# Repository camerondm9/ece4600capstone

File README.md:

# ece4600capstone
This repository is for storing files related to our Capstone project.

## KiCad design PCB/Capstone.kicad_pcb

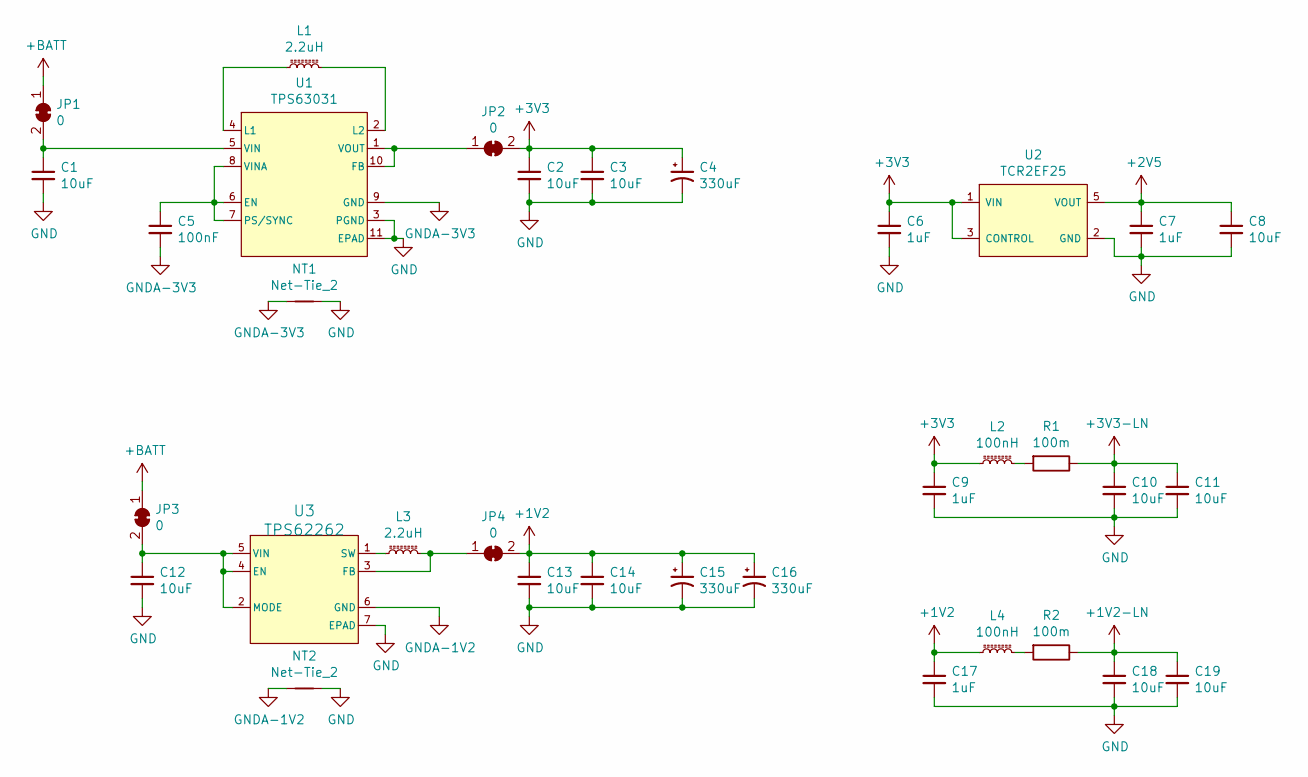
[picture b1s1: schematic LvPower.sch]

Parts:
C1, C2, C3, C8, C10, C11, C12, C13, C14, C18, C19: 10uF; C_0805_HandSoldering
C4, C15, C16: 330uF; CP_Radial_D6.3mm_P2.50mm
C5: 100nF; C_0603_HandSoldering
C6, C7, C9, C17: 1uF; C_0603_HandSoldering
JP1, JP2, JP3, JP4: 0; SolderJumper_0603
L1, L3: 2.2uH; Inductor_Taiyo-Yuden_MD-3030
L2, L4: 100nH; R_0805_HandSoldering
NT1, NT2: Net-Tie_2; NetTie-2
R1, R2: 100m; R_0805_HandSoldering
U1: TPS63031; WSON10-PAD
U2: TCR2EF25; SOT23-5
U3: TPS62262; WSON6-2x2-PAD

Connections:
+1V2: C13.1, C14.1, C15.1, C16.1, C17.1, JP4.2 (B), L4.1; also elsewhere on the board
+1V2-LN: C18.1, C19.1, R2.1; also elsewhere on the board
+2V5: C7.1, C8.1, U2.5 (VOUT); also elsewhere on the board
+3V3: C2.1, C3.1, C4.1, C6.1, C9.1, JP2.2 (B), L2.1, U2.1 (VIN), U2.3 (CONTROL); also elsewhere on the board
+3V3-LN: C10.1, C11.1, R1.1; also elsewhere on the board
+BATT: JP1.1 (A), JP3.1 (A); also elsewhere on the board
GND: C1.2, C2.2, C3.2, C4.2, C6.2, C7.2, C8.2, C9.2, C10.2, C11.2, C12.2, C13.2, C14.2, C15.2, C16.2, C17.2, C18.2, C19.2, NT1.2, NT2.2, U1.3 (PGND), U1.11 (EPAD), U2.2 (GND), U3.7 (EPAD); also elsewhere on the board
GNDA-1V2: NT2.1, U3.6 (GND)
GNDA-3V3: C5.2, NT1.1, U1.9 (GND)
unnamed: C1.1, JP1.2 (B), U1.5 (VIN)
unnamed: C5.1, U1.6 (EN), U1.7 (PS/SYNC), U1.8 (VINA)
unnamed: C12.1, JP3.2 (B), U3.2 (MODE), U3.4 (EN), U3.5 (VIN)
unnamed: JP2.1 (A), U1.1 (VOUT), U1.10 (FB)
unnamed: JP4.1 (A), L3.2, U3.3 (FB)
unnamed: L1.1, U1.4 (L1)
unnamed: L1.2, U1.2 (L2)
unnamed: L2.2, R1.2
unnamed: L3.1, U3.1 (SW)
unnamed: L4.2, R2.2

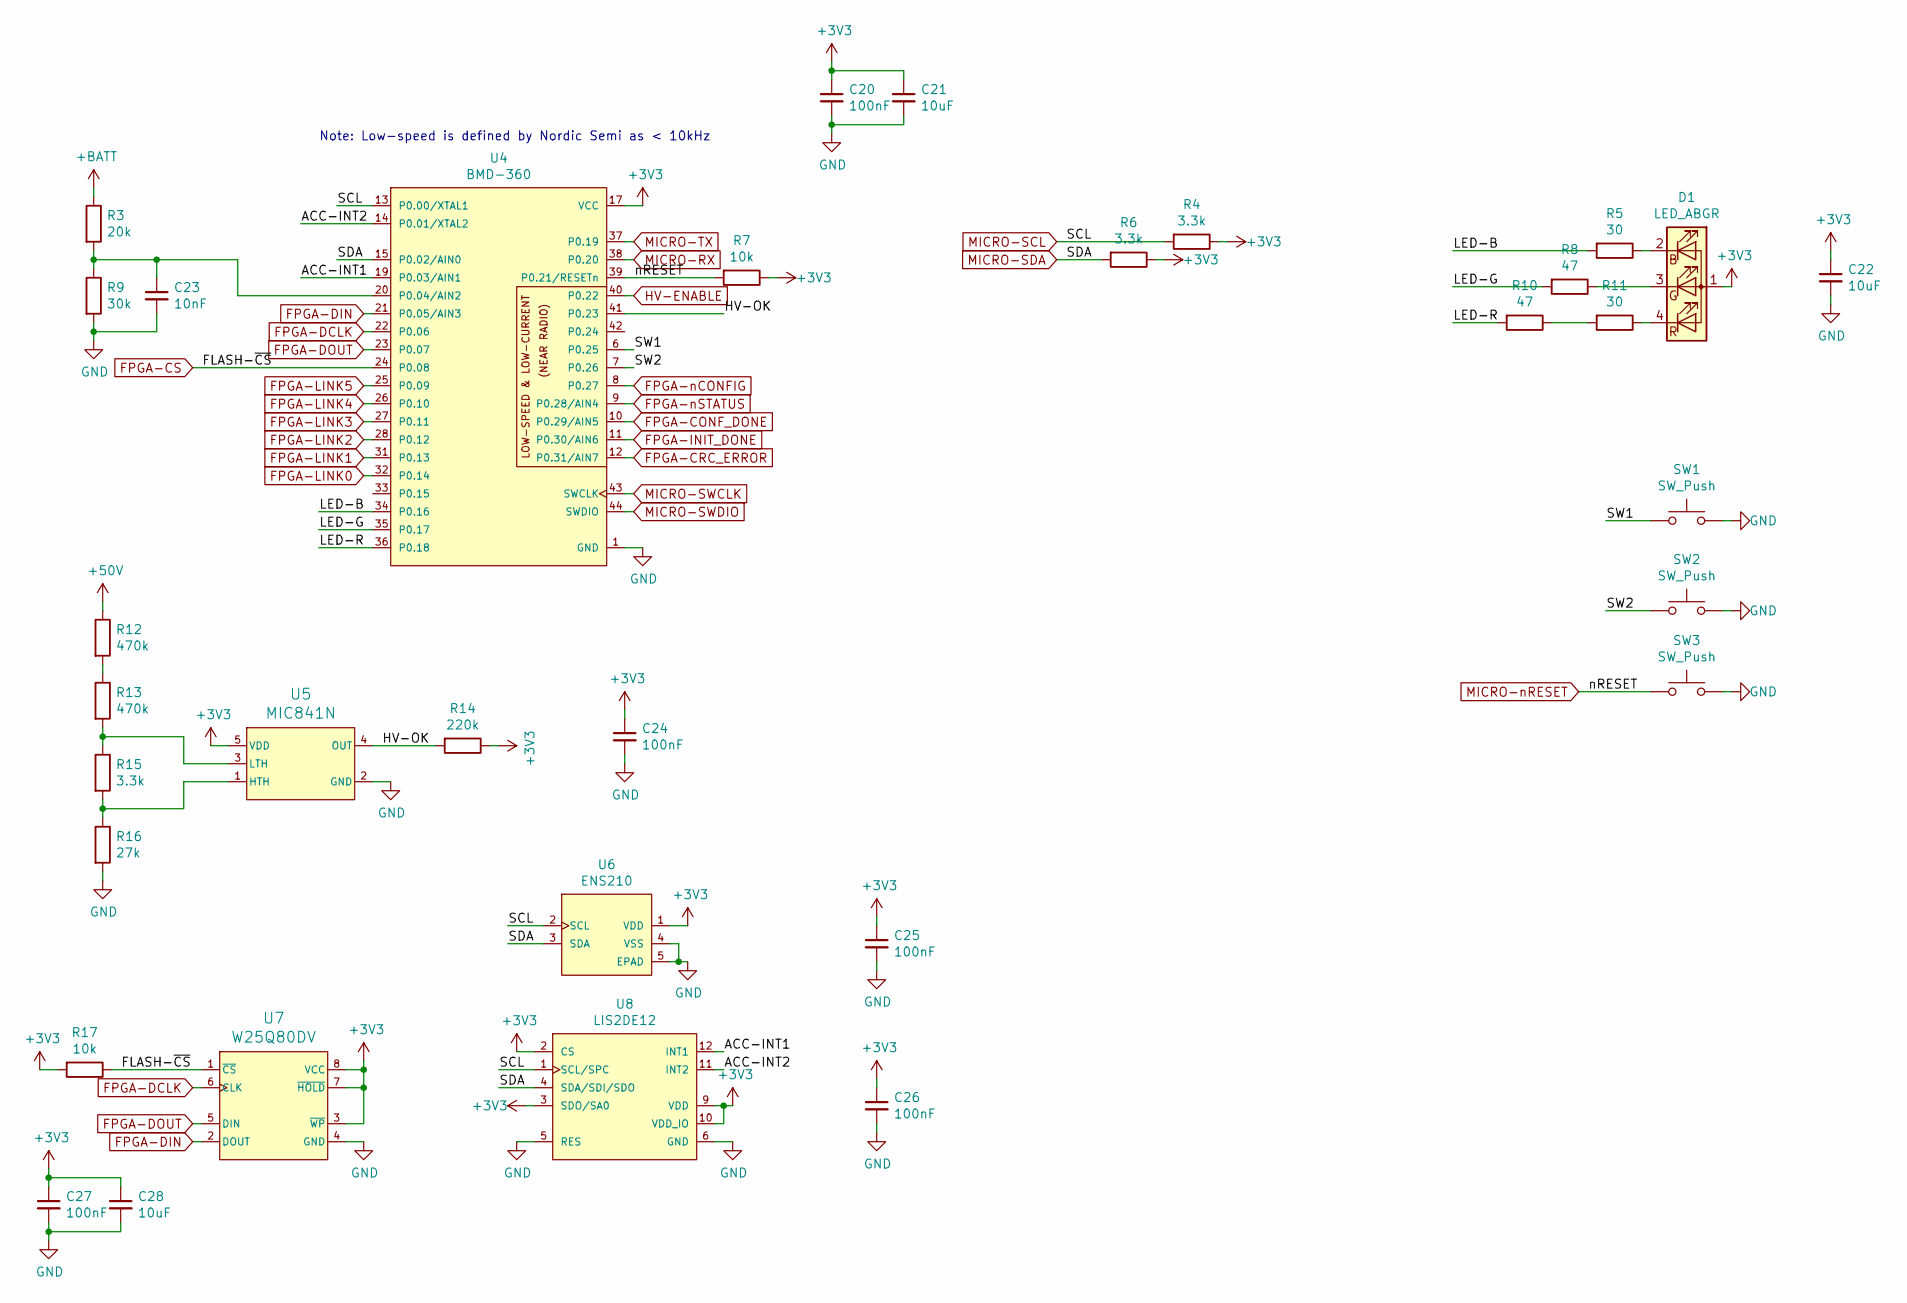
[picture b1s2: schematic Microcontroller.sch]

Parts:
C20, C24, C25, C26, C27: 100nF; C_0603_HandSoldering
C21, C22, C28: 10uF; C_0805_HandSoldering
C23: 10nF; C_0603_HandSoldering
D1: LED_ABGR; CLMVC-FKA
R3: 20k; R_0603_HandSoldering
R4, R6, R15: 3.3k; R_0603_HandSoldering
R5, R11: 30; R_0603_HandSoldering
R7, R17: 10k; R_0603_HandSoldering
R8, R10: 47; R_0603_HandSoldering
R9: 30k; R_0603_HandSoldering
R12, R13: 470k; R_0603_HandSoldering
R14: 220k; R_0603_HandSoldering
R16: 27k; R_0603_HandSoldering
SW1, SW2, SW3: SW_Push; PTS645SK43SM
U4: BMD-360
U5: MIC841N; SOT353
U6: ENS210; QFN4-PAD
U7: W25Q80DV; SOIC8
U8: LIS2DE12; LGA12

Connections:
+3V3: C20.1, C21.1, C22.1, C24.1, C25.1, C26.1, C27.1, C28.1, D1.1 (A), R4.1, R6.1, R7.1, R14.1, R17.2, U4.17 (VCC), U5.5 (VDD), U6.1 (VDD), U7.3 (~WP), U7.7 (~HOLD), U7.8 (VCC), U8.2 (CS), U8.3 (SDO/SA0), U8.9 (VDD), U8.10 (VDD_IO); also elsewhere on the board
+50V: R12.1; also elsewhere on the board
+BATT: R3.1; also elsewhere on the board
/Microcontroller/ACC-INT1: U4.19 (P0.03/AIN1), U8.12 (INT1)
/Microcontroller/ACC-INT2: U4.14 (P0.01/XTAL2), U8.11 (INT2)
/Microcontroller/HV-OK: R14.2, U4.41 (P0.23), U5.4 (OUT)
/Microcontroller/LED-B: R5.2, U4.34 (P0.16)
/Microcontroller/LED-G: R8.2, U4.35 (P0.17)
/Microcontroller/LED-R: R10.2, U4.36 (P0.18)
/Microcontroller/SW1: SW1.1, U4.6 (P0.25)
/Microcontroller/SW2: SW2.1, U4.7 (P0.26)
FPGA-CONF_DONE: U4.10 (P0.29/AIN5); also elsewhere on the board
FPGA-CRC_ERROR: U4.12 (P0.31/AIN7); also elsewhere on the board
FPGA-CS: R17.1, U4.24 (P0.08), U7.1 (~CS); also elsewhere on the board
FPGA-DCLK: U4.22 (P0.06), U7.6 (CLK); also elsewhere on the board
FPGA-DIN: U4.21 (P0.05/AIN3), U7.2 (DOUT); also elsewhere on the board
FPGA-DOUT: U4.23 (P0.07), U7.5 (DIN); also elsewhere on the board
FPGA-INIT_DONE: U4.11 (P0.30/AIN6); also elsewhere on the board
FPGA-LINK0: U4.32 (P0.14); also elsewhere on the board
FPGA-LINK1: U4.31 (P0.13); also elsewhere on the board
FPGA-LINK2: U4.28 (P0.12); also elsewhere on the board
FPGA-LINK3: U4.27 (P0.11); also elsewhere on the board
FPGA-LINK4: U4.26 (P0.10); also elsewhere on the board
FPGA-LINK5: U4.25 (P0.09); also elsewhere on the board
FPGA-nCONFIG: U4.8 (P0.27); also elsewhere on the board
FPGA-nSTATUS: U4.9 (P0.28/AIN4); also elsewhere on the board
GND: C20.2, C21.2, C22.2, C23.2, C24.2, C25.2, C26.2, C27.2, C28.2, R9.2, R16.2, SW1.2, SW2.2, SW3.2, U4.1 (GND), U4.2 (GND), U4.3 (GND), U4.4 (GND), U4.5 (GND), U4.16 (GND), U4.18 (GND), U4.29 (GND), U4.30 (GND), U4.45 (GND), U4.46 (GND), U4.47 (GND), U5.2 (GND), U6.4 (VSS), U6.5 (EPAD), U7.4 (GND), U8.5 (RES), U8.6 (GND), U8.7 (GND), U8.8 (GND); also elsewhere on the board
HV-ENABLE: U4.40 (P0.22); also elsewhere on the board
MICRO-RX: U4.38 (P0.20); also elsewhere on the board
MICRO-SCL: R4.2, U4.13 (P0.00/XTAL1), U6.2 (SCL), U8.1 (SCL/SPC); also elsewhere on the board
MICRO-SDA: R6.2, U4.15 (P0.02/AIN0), U6.3 (SDA), U8.4 (SDA/SDI/SDO); also elsewhere on the board
MICRO-SWCLK: U4.43 (SWCLK); also elsewhere on the board
MICRO-SWDIO: U4.44 (SWDIO); also elsewhere on the board
MICRO-TX: U4.37 (P0.19); also elsewhere on the board
MICRO-nRESET: R7.2, SW3.1, U4.39 (P0.21/RESETn); also elsewhere on the board
unnamed: C23.1, R3.2, R9.1, U4.20 (P0.04/AIN2)
unnamed: D1.2 (RK), R5.1
unnamed: D1.3 (GK), R8.1
unnamed: D1.4 (BK), R11.1
unnamed: R10.1, R11.2
unnamed: R12.2, R13.1
unnamed: R13.2, R15.1, U5.3 (LTH)
unnamed: R15.2, R16.1, U5.1 (HTH)

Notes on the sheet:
Note: Low-speed is defined by Nordic Semi as < 10kHz

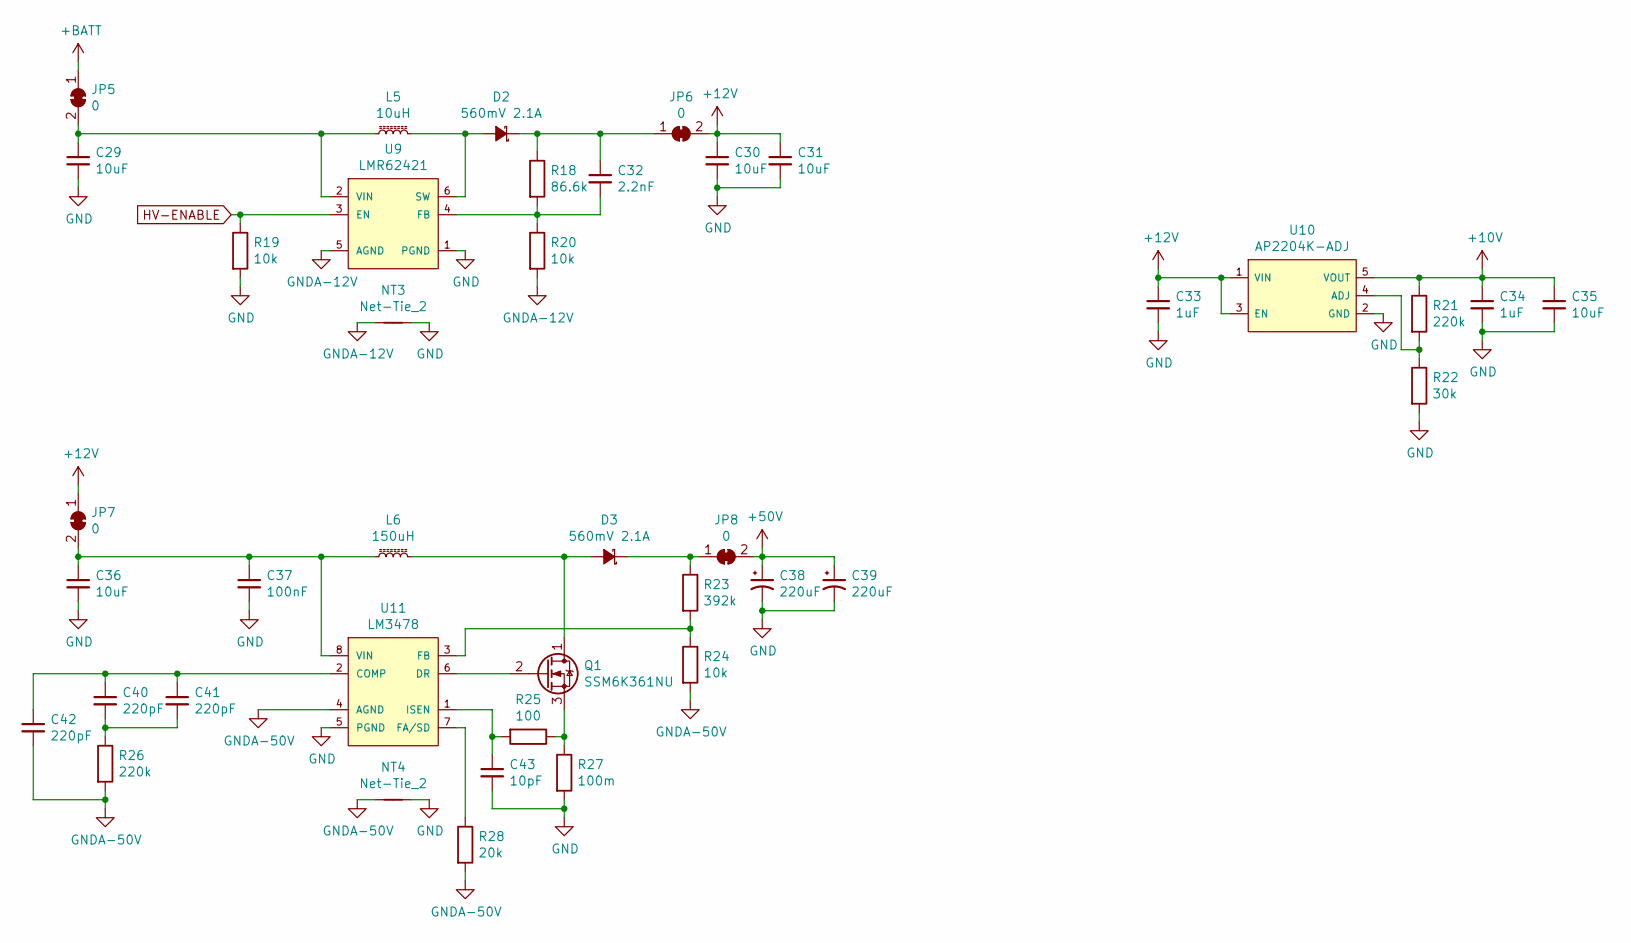
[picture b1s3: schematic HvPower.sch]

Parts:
C29: 10uF; C_0805_HandSoldering
C30, C31, C35, C36: 10uF; C_1206_HandSoldering
C32: 2.2nF; C_0603_HandSoldering
C33, C34: 1uF; C_0805_HandSoldering
C37: 100nF; C_0603_HandSoldering
C38, C39: 220uF; CP_Radial_D10.0mm_P5.00mm
C40, C41, C42: 220pF; C_0603_HandSoldering
C43: 10pF; C_0603_HandSoldering
D2, D3: 560mV 2.1A; DO-220AA
JP5, JP6, JP7, JP8: 0; SolderJumper_0603
L5: 10uH; NRS6045T100MMGK
L6: 150uH; SRU1048-151Y
NT3, NT4: Net-Tie_2; NetTie-2
Q1: SSM6K361NU; UDFN6-FET-PAD
R18: 86.6k; R_0603_HandSoldering
R19, R20, R24: 10k; R_0603_HandSoldering
R21, R26: 220k; R_0603_HandSoldering
R22: 30k; R_0603_HandSoldering
R23: 392k; R_0603_HandSoldering
R25: 100; R_0603_HandSoldering
R27: 100m; R_0603_HandSoldering
R28: 20k; R_0603_HandSoldering
U9: LMR62421; WSON6-3x3-PAD
U10: AP2204K-ADJ; SOT23-5
U11: LM3478; SSOP8

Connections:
+10V: C34.1, C35.1, R21.1, U10.5 (VOUT); also elsewhere on the board
+12V: C30.1, C31.1, C33.1, JP6.2 (B), JP7.1 (A), U10.1 (VIN), U10.3 (EN); also elsewhere on the board
+50V: C38.1, C39.1, JP8.2 (B); also elsewhere on the board
+BATT: JP5.1 (A); also elsewhere on the board
GND: C29.2, C30.2, C31.2, C33.2, C34.2, C35.2, C36.2, C37.2, C38.2, C39.2, C43.2, NT3.2, NT4.2, R19.2, R22.2, R27.2, U9.1 (PGND), U9.7 (EPAD), U10.2 (GND), U11.5 (PGND); also elsewhere on the board
GNDA-12V: NT3.1, R20.2, U9.5 (AGND)
GNDA-50V: C42.2, NT4.1, R24.2, R26.2, R28.2, U11.4 (AGND)
HV-ENABLE: R19.1, U9.3 (EN); also elsewhere on the board
unnamed: C29.1, JP5.2 (B), L5.1, U9.2 (VIN)
unnamed: C32.1, D2.1 (K), JP6.1 (A), R18.1
unnamed: C32.2, R18.2, R20.1, U9.4 (FB)
unnamed: C36.1, C37.1, JP7.2 (B), L6.1, U11.8 (VIN)
unnamed: C40.1, C41.1, C42.1, U11.2 (COMP)
unnamed: C40.2, C41.2, R26.1
unnamed: C43.1, R25.2, U11.1 (ISEN)
unnamed: D2.2 (A), L5.2, U9.6 (SW)
unnamed: D3.1 (K), JP8.1 (A), R23.1
unnamed: D3.2 (A), L6.2, Q1.1 (D)
unnamed: Q1.2 (G), U11.6 (DR)
unnamed: Q1.3 (S), R25.1, R27.1
unnamed: R21.2, R22.1, U10.4 (ADJ)
unnamed: R23.2, R24.1, U11.3 (FB)
unnamed: R28.1, U11.7 (FA/SD)

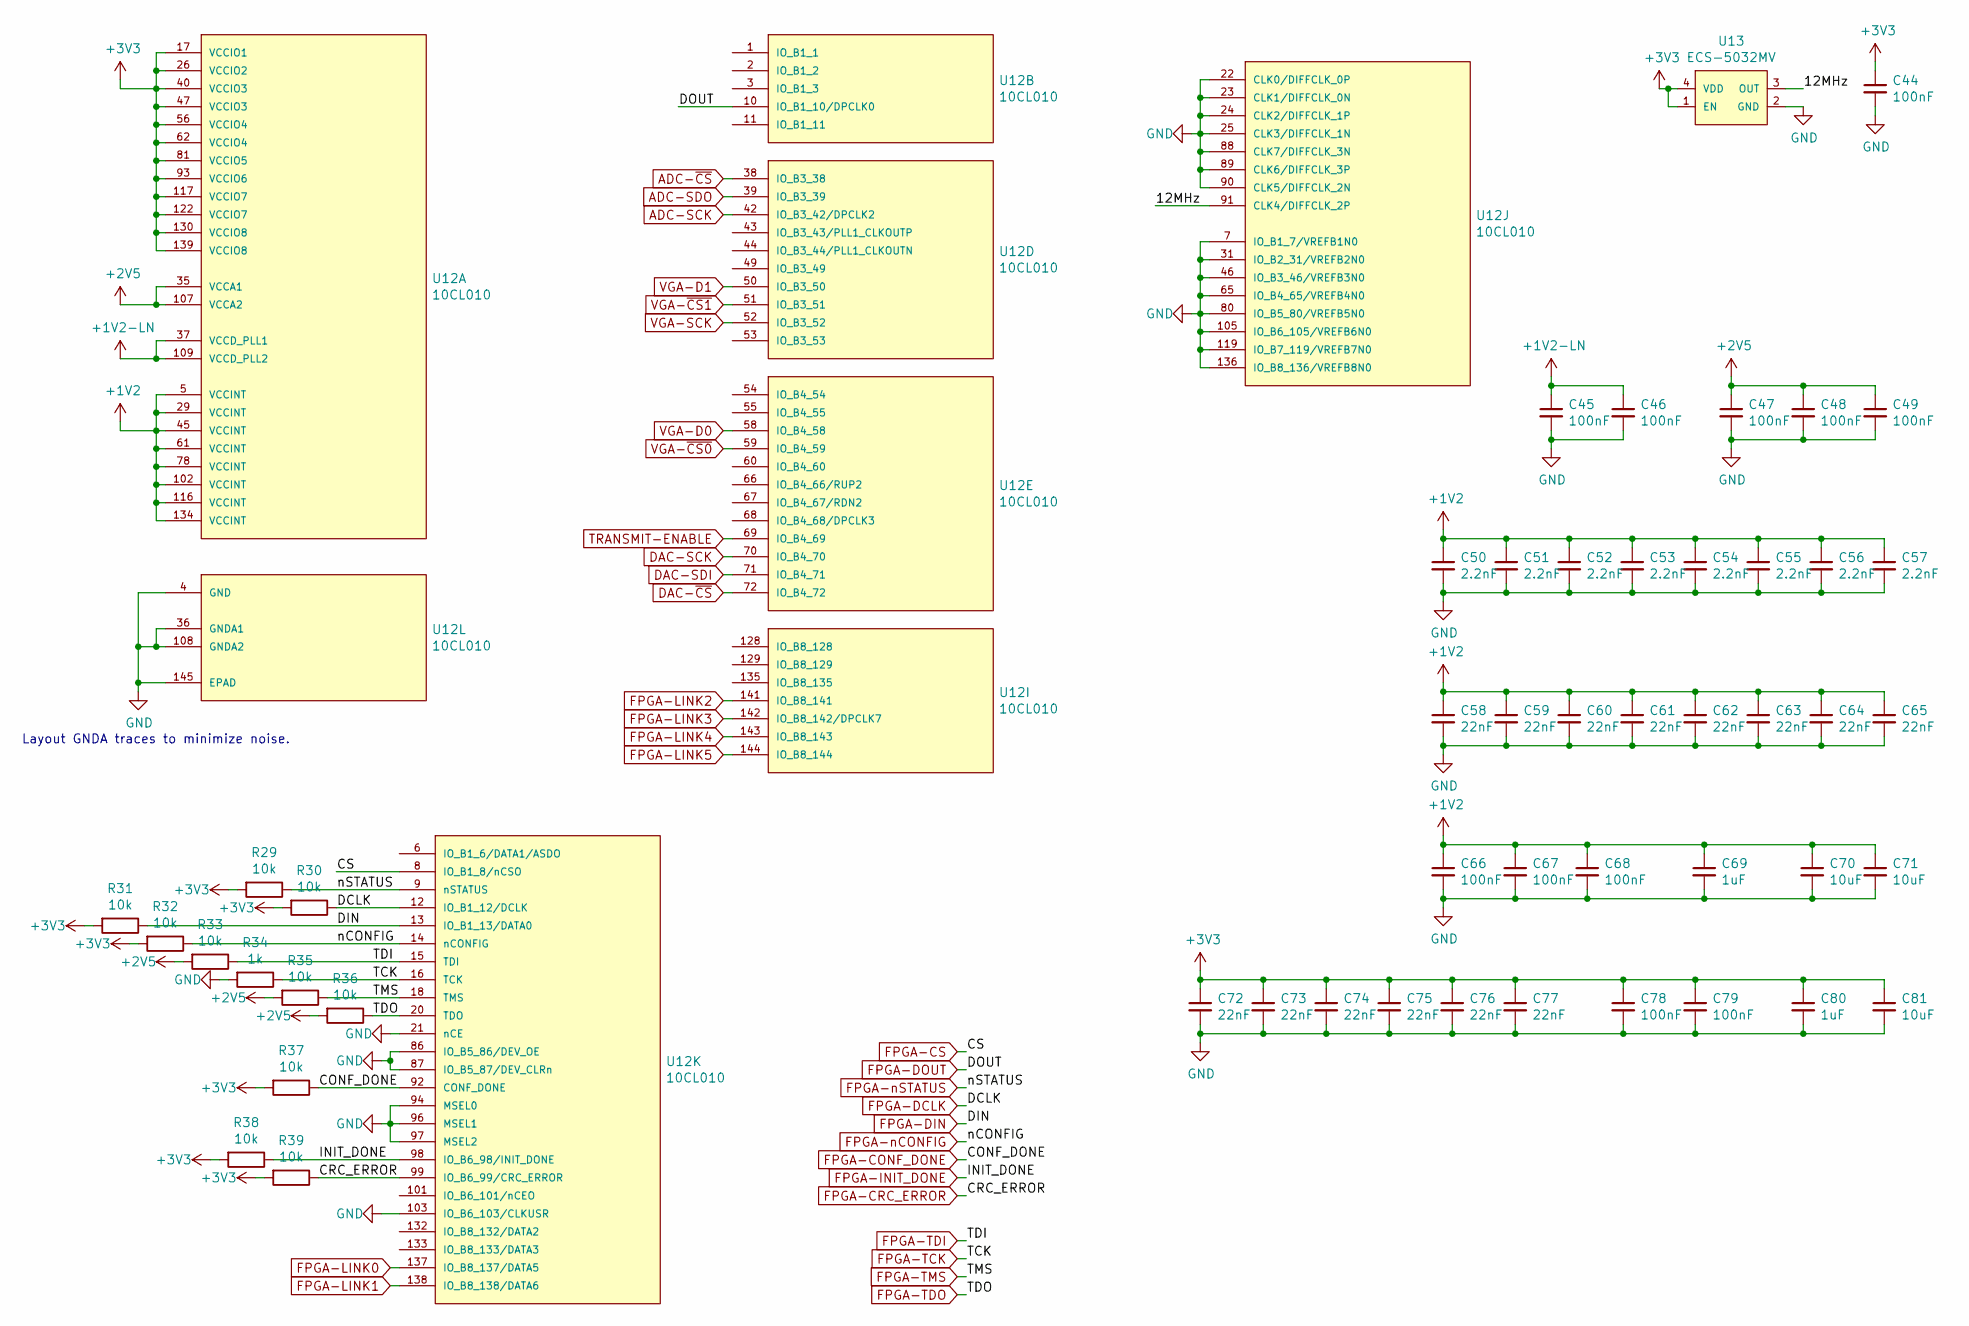
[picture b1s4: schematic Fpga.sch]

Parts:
C44, C45, C46, C47, C48, C49, C66, C67, C68, C78, C79: 100nF; C_0603_HandSoldering
C50, C51, C52, C53, C54, C55, C56, C57: 2.2nF; C_0603_HandSoldering
C58, C59, C60, C61, C62, C63, C64, C65, C72, C73, C74, C75, C76, C77: 22nF; C_0603_HandSoldering
C69, C80: 1uF; C_0603_HandSoldering
C70, C71, C81: 10uF; C_0805_HandSoldering
R29, R30, R31, R32, R33, R35, R36, R37, R38, R39: 10k; R_0603_HandSoldering
R34: 1k; R_0603_HandSoldering
U12: 10CL010; EQFP144-PAD
U13: ECS-5032MV

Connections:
+1V2: C50.1, C51.1, C52.1, C53.1, C54.1, C55.1, C56.1, C57.1, C58.1, C59.1, C60.1, C61.1, C62.1, C63.1, C64.1, C65.1, C66.1, C67.1, C68.1, C69.1, C70.1, C71.1, U12.5 (VCCINT), U12.29 (VCCINT), U12.45 (VCCINT), U12.61 (VCCINT), U12.78 (VCCINT), U12.102 (VCCINT), U12.116 (VCCINT), U12.134 (VCCINT); also elsewhere on the board
+1V2-LN: C45.1, C46.1, U12.37 (VCCD_PLL1), U12.109 (VCCD_PLL2); also elsewhere on the board
+2V5: C47.1, C48.1, C49.1, R33.2, R35.2, R36.2, U12.35 (VCCA1), U12.107 (VCCA2); also elsewhere on the board
+3V3: C44.1, C72.1, C73.1, C74.1, C75.1, C76.1, C77.1, C78.1, C79.1, C80.1, C81.1, R29.2, R30.2, R31.2, R32.2, R37.2, R38.2, R39.2, U12.17 (VCCIO1), U12.26 (VCCIO2), U12.40 (VCCIO3), U12.47 (VCCIO3), U12.56 (VCCIO4), U12.62 (VCCIO4), U12.81 (VCCIO5), U12.93 (VCCIO6), U12.117 (VCCIO7), U12.122 (VCCIO7), U12.130 (VCCIO8), U12.139 (VCCIO8), U13.1 (EN), U13.4 (VDD); also elsewhere on the board
/Fpga/12MHz: U12.91 (CLK4/DIFFCLK_2P), U13.3 (OUT)
ADC-SCK: U12.42 (IO_B3_42/DPCLK2); also elsewhere on the board
ADC-SDO: U12.39 (IO_B3_39); also elsewhere on the board
ADC-~CS: U12.38 (IO_B3_38); also elsewhere on the board
DAC-SCK: U12.70 (IO_B4_70); also elsewhere on the board
DAC-SDI: U12.71 (IO_B4_71); also elsewhere on the board
DAC-~CS: U12.72 (IO_B4_72); also elsewhere on the board
FPGA-CONF_DONE: R37.1, U12.92 (CONF_DONE); also elsewhere on the board
FPGA-CRC_ERROR: R39.1, U12.99 (IO_B6_99/CRC_ERROR); also elsewhere on the board
FPGA-CS: U12.8 (IO_B1_8/nCSO); also elsewhere on the board
FPGA-DCLK: R30.1, U12.12 (IO_B1_12/DCLK); also elsewhere on the board
FPGA-DIN: R31.1, U12.13 (IO_B1_13/DATA0); also elsewhere on the board
FPGA-DOUT: U12.10 (IO_B1_10/DPCLK0); also elsewhere on the board
FPGA-INIT_DONE: R38.1, U12.98 (IO_B6_98/INIT_DONE); also elsewhere on the board
FPGA-LINK0: U12.137 (IO_B8_137/DATA5); also elsewhere on the board
FPGA-LINK1: U12.138 (IO_B8_138/DATA6); also elsewhere on the board
FPGA-LINK2: U12.141 (IO_B8_141); also elsewhere on the board
FPGA-LINK3: U12.142 (IO_B8_142/DPCLK7); also elsewhere on the board
FPGA-LINK4: U12.143 (IO_B8_143); also elsewhere on the board
FPGA-LINK5: U12.144 (IO_B8_144); also elsewhere on the board
FPGA-TCK: R34.1, U12.16 (TCK); also elsewhere on the board
FPGA-TDI: R33.1, U12.15 (TDI); also elsewhere on the board
FPGA-TDO: R36.1, U12.20 (TDO); also elsewhere on the board
FPGA-TMS: R35.1, U12.18 (TMS); also elsewhere on the board
FPGA-nCONFIG: R32.1, U12.14 (nCONFIG); also elsewhere on the board
FPGA-nSTATUS: R29.1, U12.9 (nSTATUS); also elsewhere on the board
GND: C44.2, C45.2, C46.2, C47.2, C48.2, C49.2, C50.2, C51.2, C52.2, C53.2, C54.2, C55.2, C56.2, C57.2, C58.2, C59.2, C60.2, C61.2, C62.2, C63.2, C64.2, C65.2, C66.2, C67.2, C68.2, C69.2, C70.2, C71.2, C72.2, C73.2, C74.2, C75.2, C76.2, C77.2, C78.2, C79.2, C80.2, C81.2, R34.2, U12.4 (GND), U12.7 (IO_B1_7/VREFB1N0), U12.19 (GND), U12.21 (nCE), U12.22 (CLK0/DIFFCLK_0P), U12.23 (CLK1/DIFFCLK_0N), U12.24 (CLK2/DIFFCLK_1P), U12.25 (CLK3/DIFFCLK_1N), U12.27 (GND), U12.30 (GND), U12.31 (IO_B2_31/VREFB2N0), U12.36 (GNDA1), U12.41 (GND), U12.46 (IO_B3_46/VREFB3N0), U12.48 (GND), U12.57 (GND), U12.63 (GND), U12.64 (GND), U12.65 (IO_B4_65/VREFB4N0), U12.79 (GND), U12.80 (IO_B5_80/VREFB5N0), U12.82 (GND), U12.86 (IO_B5_86/DEV_OE), U12.87 (IO_B5_87/DEV_CLRn), U12.88 (CLK7/DIFFCLK_3N), U12.89 (CLK6/DIFFCLK_3P), U12.90 (CLK5/DIFFCLK_2N), U12.94 (MSEL0), U12.95 (GND), U12.96 (MSEL1), U12.97 (MSEL2), U12.103 (IO_B6_103/CLKUSR), U12.104 (GND), U12.105 (IO_B6_105/VREFB6N0), U12.108 (GNDA2), U12.110 (GND), U12.118 (GND), U12.119 (IO_B7_119/VREFB7N0), U12.123 (GND), U12.131 (GND), U12.136 (IO_B8_136/VREFB8N0), U12.140 (GND), U12.145 (EPAD), U13.2 (GND); also elsewhere on the board
TRANSMIT-ENABLE: U12.69 (IO_B4_69); also elsewhere on the board
VGA-D0: U12.58 (IO_B4_58); also elsewhere on the board
VGA-D1: U12.50 (IO_B3_50); also elsewhere on the board
VGA-SCK: U12.52 (IO_B3_52); also elsewhere on the board
VGA-~CS0: U12.59 (IO_B4_59); also elsewhere on the board
VGA-~CS1: U12.51 (IO_B3_51); also elsewhere on the board

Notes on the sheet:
Layout GNDA traces to minimize noise.

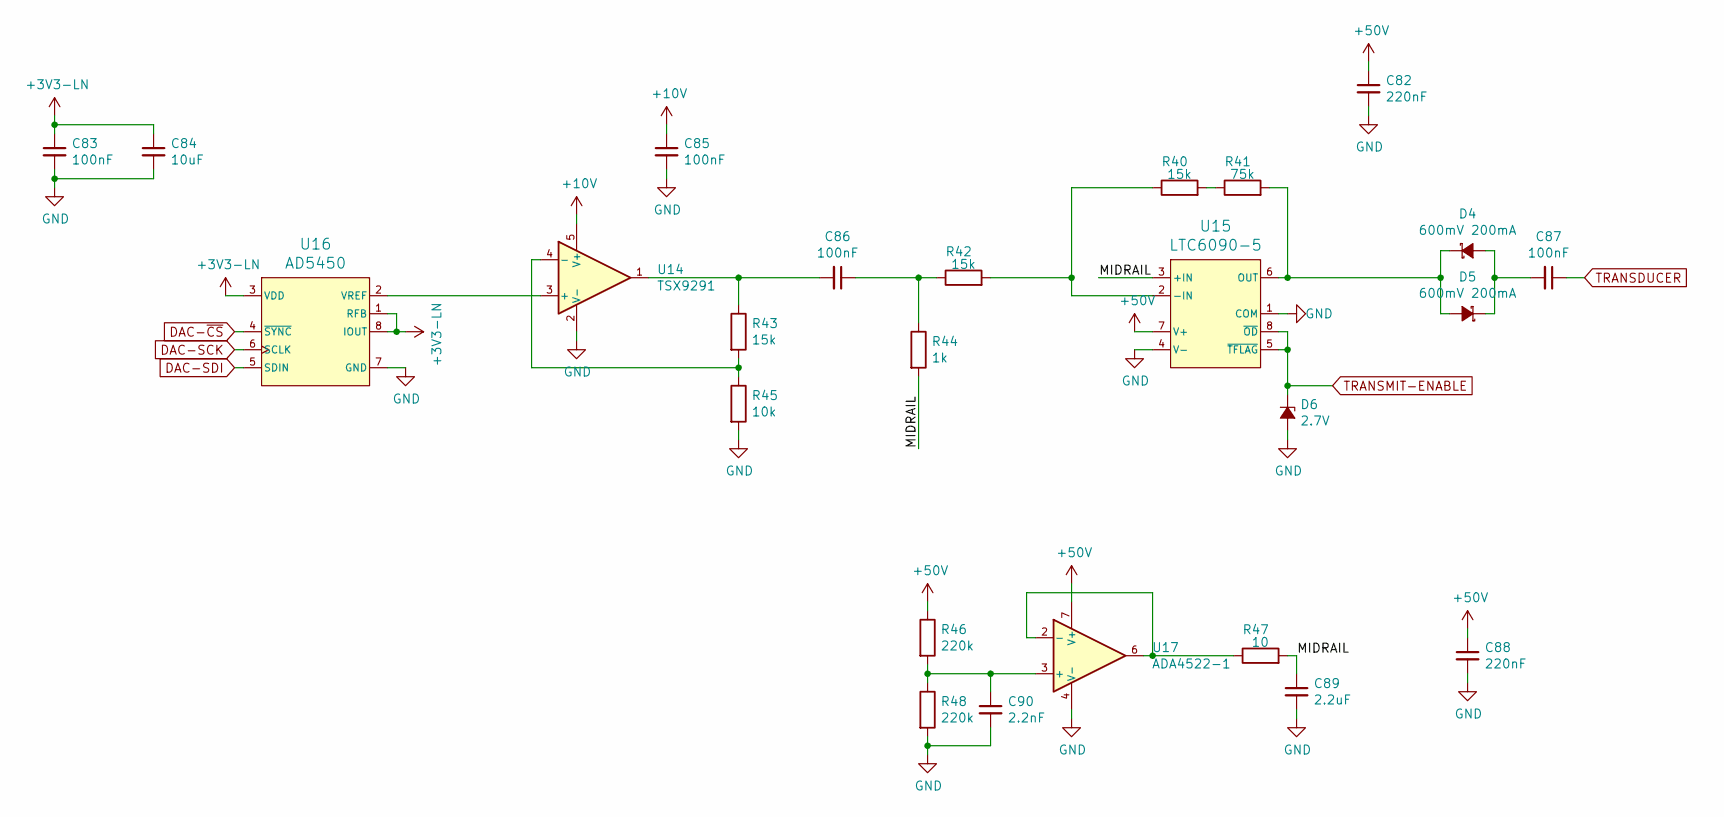
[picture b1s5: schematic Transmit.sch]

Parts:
C82, C88: 220nF; C_1206_HandSoldering
C83, C85: 100nF; C_0603_HandSoldering
C84: 10uF; C_0805_HandSoldering
C86, C87: 100nF; C_1206_HandSoldering
C89: 2.2uF; C_1206_HandSoldering
C90: 2.2nF; C_0603_HandSoldering
D4, D5: 600mV 200mA; D_SOD-523
D6: 2.7V; D_SOD-123
R40, R42, R43: 15k; R_0603_HandSoldering
R41: 75k; R_0603_HandSoldering
R44: 1k; R_0603_HandSoldering
R45: 10k; R_0603_HandSoldering
R46, R48: 220k; R_0603_HandSoldering
R47: 10; R_0603_HandSoldering
U14: TSX9291; SOT23-5
U15: LTC6090-5; SOIC8-PAD
U16: AD5450; TSOT8
U17: ADA4522-1; SSOP8

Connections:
+3V3-LN: C83.1, C84.1, U16.1 (RFB), U16.3 (VDD), U16.8 (IOUT); also elsewhere on the board
+10V: C85.1, U14.5 (V+); also elsewhere on the board
+50V: C82.1, C88.1, R46.1, U15.7 (V+), U17.7 (V+); also elsewhere on the board
/Transmit/MIDRAIL: C89.1, R44.2, R47.2, U15.3 (+IN)
DAC-SCK: U16.6 (SCLK); also elsewhere on the board
DAC-SDI: U16.5 (SDIN); also elsewhere on the board
DAC-~CS: U16.4 (~SYNC); also elsewhere on the board
GND: C82.2, C83.2, C84.2, C85.2, C88.2, C89.2, C90.2, D6.2 (A), R45.2, R48.2, U14.2 (V-), U15.1 (COM), U15.4 (V-), U15.9 (EPAD), U16.7 (GND), U17.4 (V-); also elsewhere on the board
unnamed: C86.1, R42.1, R44.1
unnamed: C86.2, R43.1, U14.1
unnamed: C87.2, D4.2 (A), D5.1 (K)
unnamed: C90.1, R46.2, R48.1, U17.3 (+)
unnamed: D4.1 (K), D5.2 (A), R41.2, U15.6 (OUT)
unnamed: R40.1, R42.2, U15.2 (-IN)
unnamed: R40.2, R41.1
unnamed: R43.2, R45.1, U14.4 (-)
unnamed: R47.1, U17.2 (-), U17.6
unnamed: U14.3 (+), U16.2 (VREF)
TRANSDUCER: C87.1; also elsewhere on the board
TRANSMIT-ENABLE: D6.1 (K), U15.5 (~TFLAG), U15.8 (~OD); also elsewhere on the board

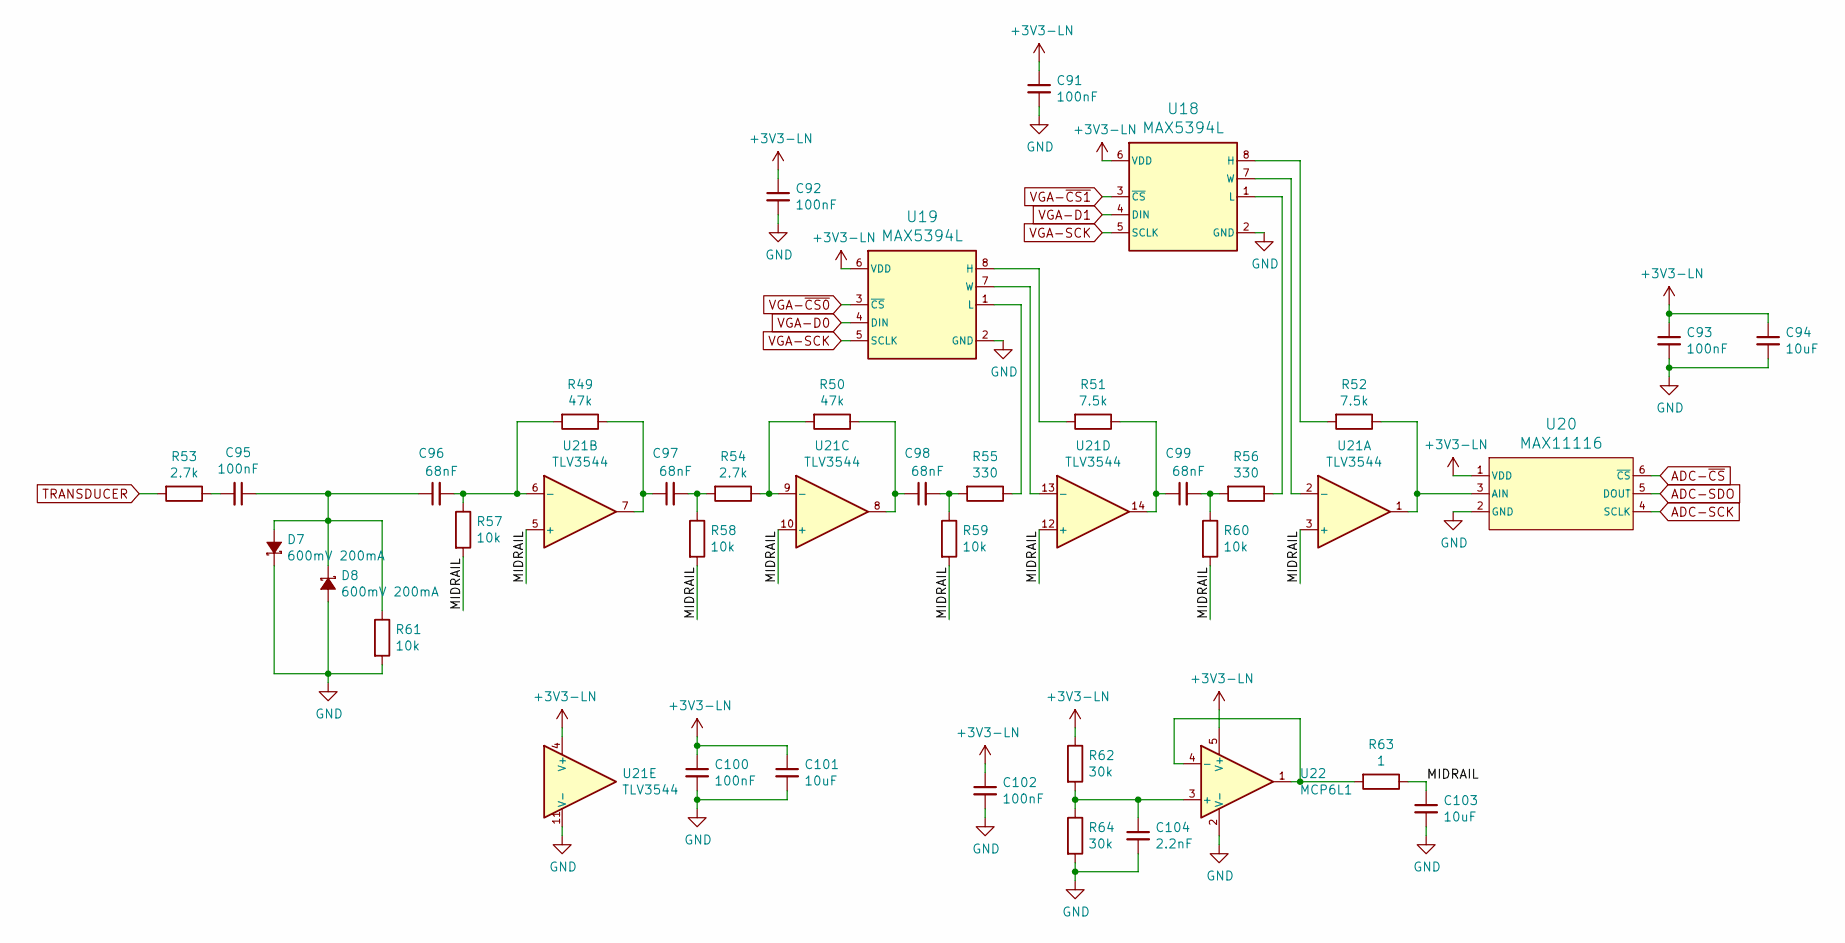
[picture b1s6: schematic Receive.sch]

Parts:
C91, C92, C93, C100, C102: 100nF; C_0603_HandSoldering
C94, C101, C103: 10uF; C_0805_HandSoldering
C95: 100nF; C_1206_HandSoldering
C96, C97, C98, C99: 68nF; C_0805_HandSoldering
C104: 2.2nF; C_0603_HandSoldering
D7, D8: 600mV 200mA; D_SOD-523
R49, R50: 47k; R_0603_HandSoldering
R51, R52: 7.5k; R_0603_HandSoldering
R53, R54: 2.7k; R_0603_HandSoldering
R55, R56: 330; R_0603_HandSoldering
R57, R58, R59, R60, R61: 10k; R_0603_HandSoldering
R62, R64: 30k; R_0603_HandSoldering
R63: 1; R_0603_HandSoldering
U18, U19: MAX5394L; TDFN8-PAD
U20: MAX11116; SOT23
U21: TLV3544; SSOP14
U22: MCP6L1; SOT23-5

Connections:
+3V3-LN: C91.1, C92.1, C93.1, C94.1, C100.1, C101.1, C102.1, R62.1, U18.6 (VDD), U19.6 (VDD), U20.1 (VDD), U21.4 (V+), U22.5 (V+); also elsewhere on the board
/Receive/MIDRAIL: C103.1, R57.2, R58.2, R59.2, R60.2, R63.1, U21.3 (+), U21.5 (+), U21.10 (+), U21.12 (+)
ADC-SCK: U20.4 (SCLK); also elsewhere on the board
ADC-SDO: U20.5 (DOUT); also elsewhere on the board
ADC-~CS: U20.6 (~CS); also elsewhere on the board
GND: C91.2, C92.2, C93.2, C94.2, C100.2, C101.2, C102.2, C103.2, C104.2, D7.1 (K), D8.2 (A), R61.2, R64.2, U18.2 (GND), U18.9 (EPAD), U19.2 (GND), U19.9 (EPAD), U20.2 (GND), U21.11 (V-), U22.2 (V-); also elsewhere on the board
unnamed: C95.1, C96.1, D7.2 (A), D8.1 (K), R61.1
unnamed: C95.2, R53.1
unnamed: C96.2, R49.2, R57.1, U21.6 (-)
unnamed: C97.1, R49.1, U21.7
unnamed: C97.2, R54.2, R58.1
unnamed: C98.1, R50.1, U21.8
unnamed: C98.2, R55.2, R59.1
unnamed: C99.1, R51.1, U21.14
unnamed: C99.2, R56.2, R60.1
unnamed: C104.1, R62.2, R64.1, U22.3 (+)
unnamed: R50.2, R54.1, U21.9 (-)
unnamed: R51.2, U19.8 (H)
unnamed: R52.1, U20.3 (AIN), U21.1
unnamed: R52.2, U18.8 (H)
unnamed: R55.1, U19.1 (L)
unnamed: R56.1, U18.1 (L)
unnamed: R63.2, U22.1, U22.4 (-)
unnamed: U18.7 (W), U21.2 (-)
unnamed: U19.7 (W), U21.13 (-)
TRANSDUCER: R53.2; also elsewhere on the board
VGA-D0: U19.4 (DIN); also elsewhere on the board
VGA-D1: U18.4 (DIN); also elsewhere on the board
VGA-SCK: U18.5 (SCLK), U19.5 (SCLK); also elsewhere on the board
VGA-~CS0: U19.3 (~CS); also elsewhere on the board
VGA-~CS1: U18.3 (~CS); also elsewhere on the board
